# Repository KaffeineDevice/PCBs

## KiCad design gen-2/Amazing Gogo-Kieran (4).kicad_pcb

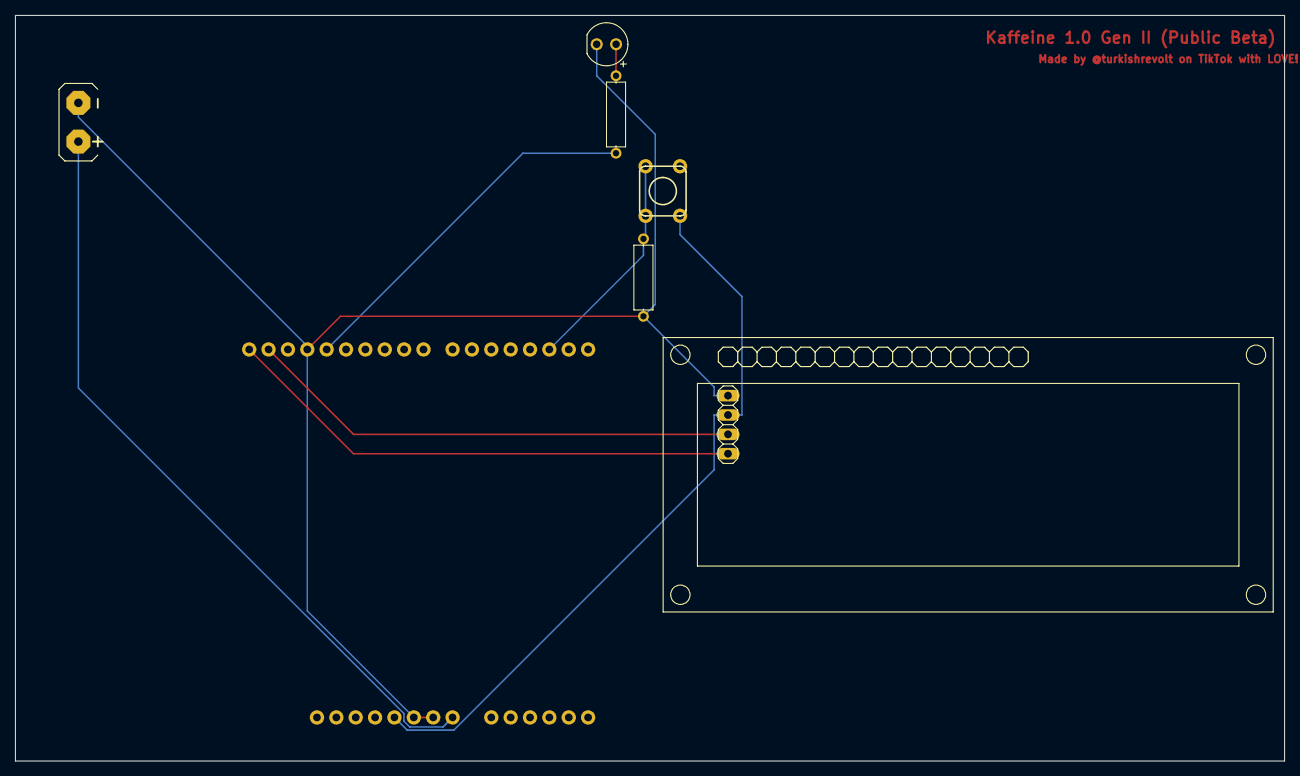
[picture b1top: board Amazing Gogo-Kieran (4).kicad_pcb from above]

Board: 2 copper layers, 166.4 x 97.8 mm, 7 parts (0 on the bottom side), 8 nets.

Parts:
BAT2: 9V; BATTERY-GENERIC
D1: LED_GREEN; LEDRD254W60D565H860B_G
R1, R2: 1k; RESAD1016W63L850D250B
S1: SWITCH_MOMENTARY; SWITCH-MOMENTARY-PTH-6.5MM
U3: ARDUINO-UNO-R3-SHIELD
U4: LCD-16X2-I2CSUNFOUNDER-IIC; LCD-I2C

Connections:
BAT2+: BAT2.+, U3.VIN
BAT2-: BAT2.-, D1.2, R2.1, U3.GND@0, U3.GND@1, U3.GND@2, U4.1
D1_A: D1.1, R1.2
U3_5V: S1.3, U3.5V, U4.2
U3_D2: R2.2, S1.1, S1.2, U3.D2
U3_D13: R1.1, U3.D13
U3_SCL: U3.SCL, U4.4
U3_SDA: U3.SDA, U4.3
